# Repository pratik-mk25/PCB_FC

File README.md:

# PCB_FC
FLIGHT CONTROLLER DEMO

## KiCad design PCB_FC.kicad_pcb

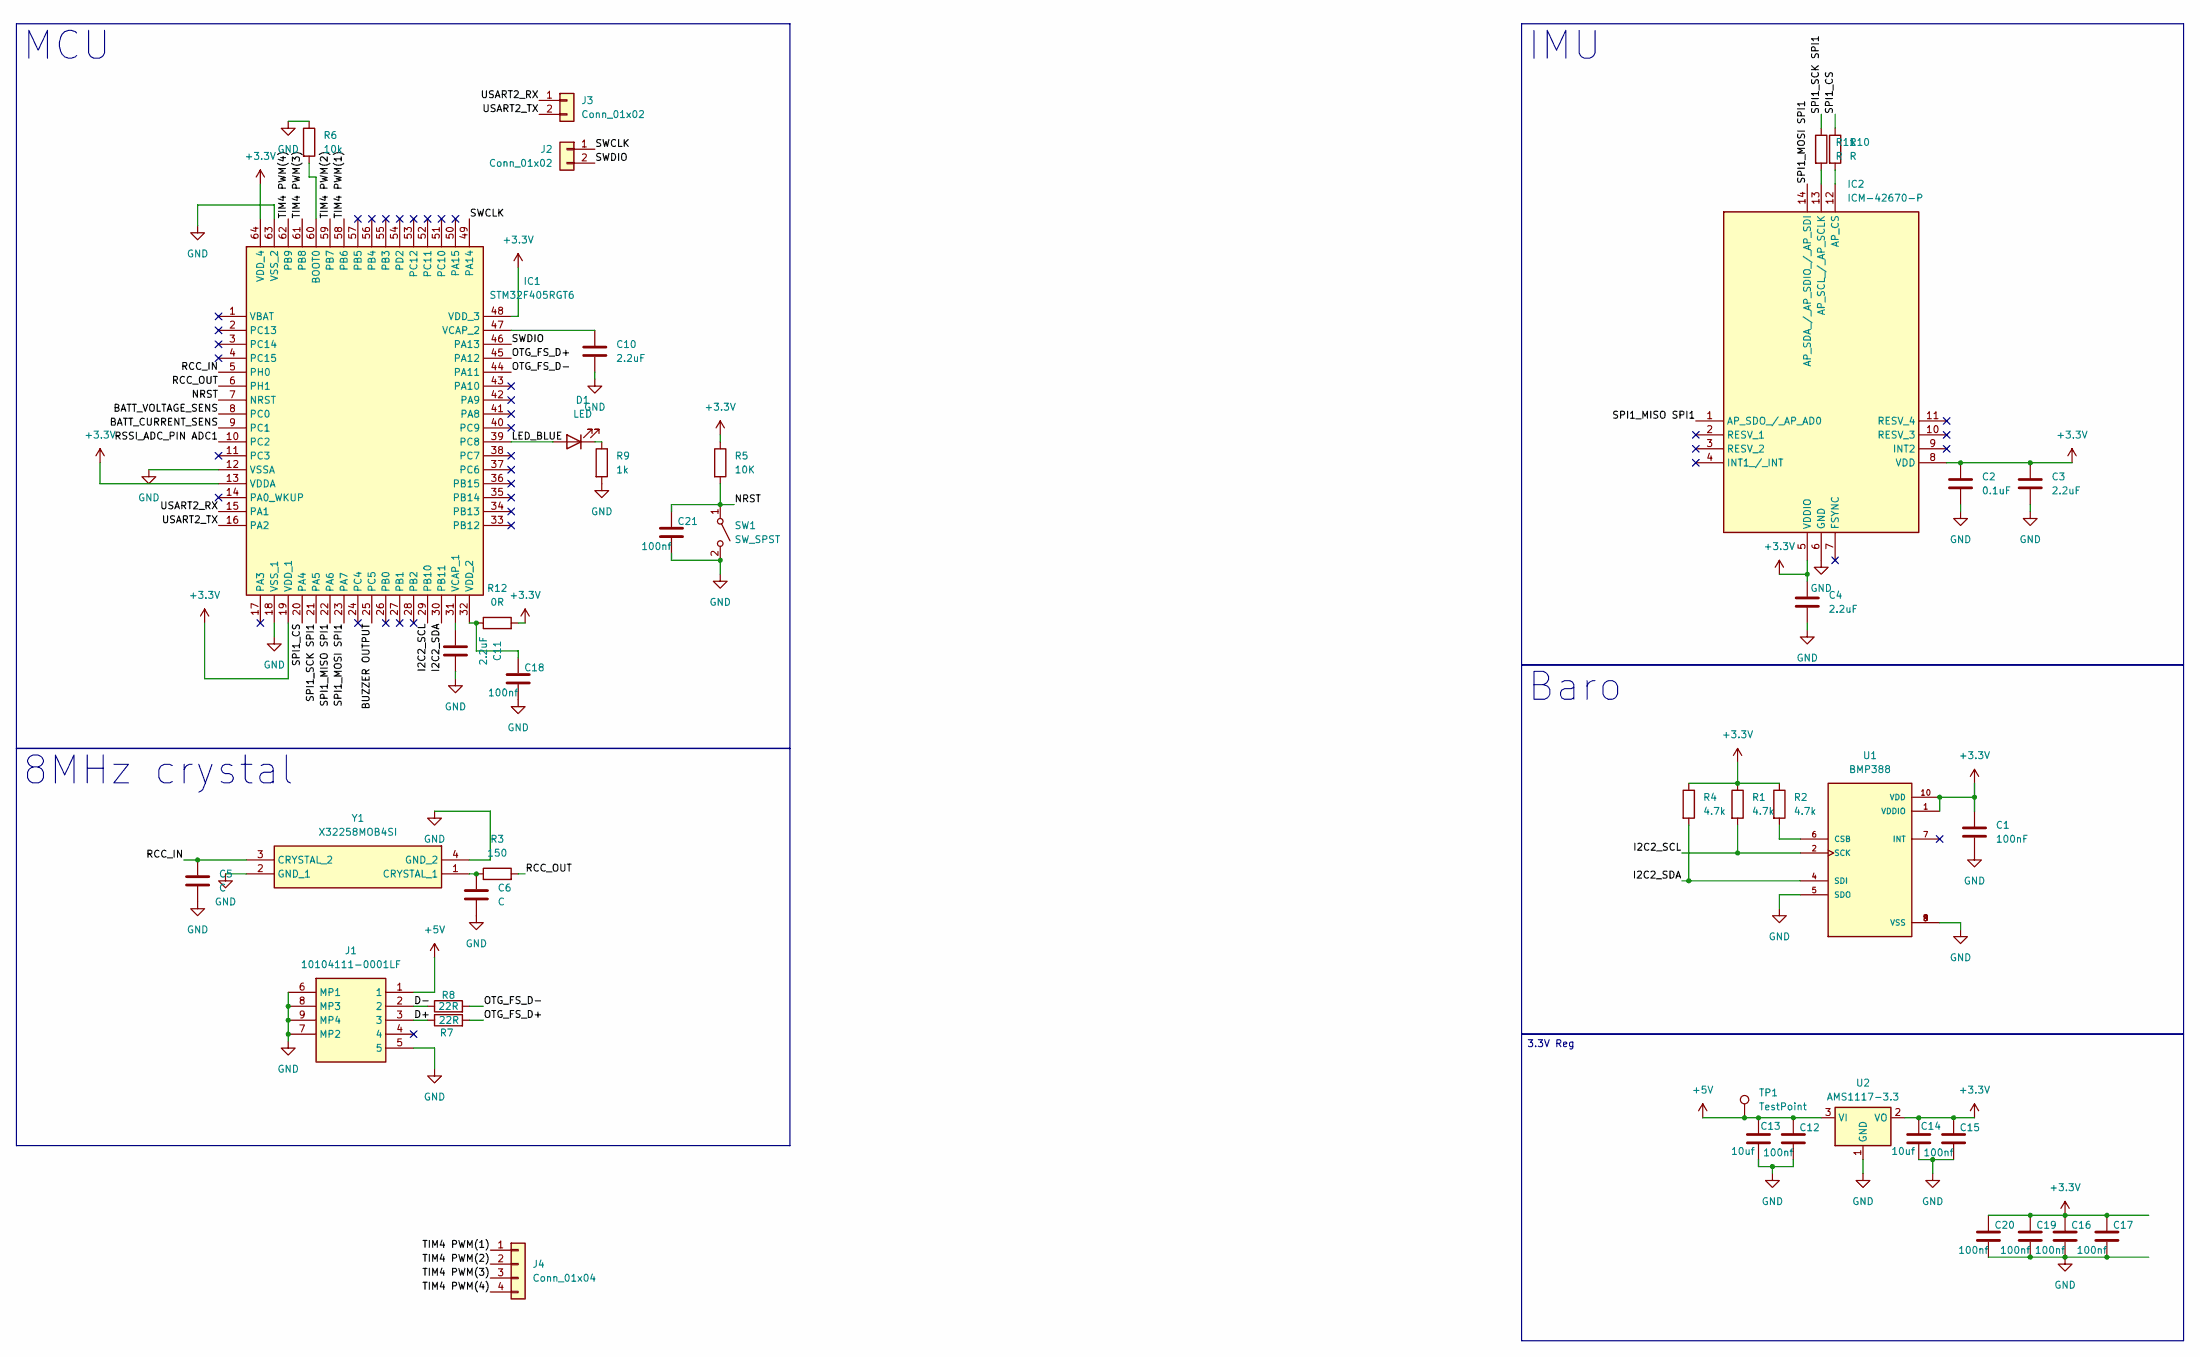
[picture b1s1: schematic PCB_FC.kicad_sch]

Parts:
C1: 100nF; C_0603_1608Metric_Pad1.08x0.95mm_HandSolder
C2: 0.1uF; C_0603_1608Metric_Pad1.08x0.95mm_HandSolder
C3, C4, C10, C11: 2.2uF; C_0603_1608Metric_Pad1.08x0.95mm_HandSolder
C5, C6: C; C_0603_1608Metric_Pad1.08x0.95mm_HandSolder
C12, C15, C16, C17, C18, C19, C20, C21: 100nf; C_0603_1608Metric_Pad1.08x0.95mm_HandSolder
C13, C14: 10uf; C_0805_2012Metric_Pad1.18x1.45mm_HandSolder
D1: LED; LED_0402_1005Metric_Pad0.77x0.64mm_HandSolder
IC1: STM32F405RGT6; Manufacturer_Part_Number STM32F405RGT6; Mouser Part Number 511-STM32F405RGT6
IC2: ICM-42670-P; Manufacturer_Part_Number ICM-42670-P; Mouser Part Number 410-ICM-42670-P
J1: 10104111-0001LF; Manufacturer_Part_Number 10104111-0001LF
J2, J3: Conn_01x02; PinHeader_1x02_P2.54mm_Vertical
J4: Conn_01x04
R1, R2, R4: 4.7k; R_0603_1608Metric_Pad0.98x0.95mm_HandSolder
R3: 150; R_0603_1608Metric_Pad0.98x0.95mm_HandSolder
R5: 10K; R_0603_1608Metric_Pad0.98x0.95mm_HandSolder
R6: 10k; R_0603_1608Metric_Pad0.98x0.95mm_HandSolder
R7, R8: 22R; R_0402_1005Metric_Pad0.72x0.64mm_HandSolder
R9: 1k; R_0603_1608Metric_Pad0.98x0.95mm_HandSolder
R10, R11: R; R_1206_3216Metric_Pad1.30x1.75mm_HandSolder
R12: 0R; R_0603_1608Metric_Pad0.98x0.95mm_HandSolder
SW1: SW_SPST; PTS636SKG25JSMTRLFS
TP1: TestPoint; Pin_D1.3mm_L11.3mm_W2.8mm_Flat
U1: BMP388; PARTREV 1.1
U2: AMS1117-3.3; SOT-223-3_TabPin2
Y1: X32258MOB4SI; Manufacturer_Part_Number X32258MOB4SI

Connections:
+3.3V: C1.1, C2.1, C3.1, C4.1, C14.1, C15.1, C16.1, C17.1, C19.1, C20.1, IC1.13 (VDDA), IC1.19 (VDD_1), IC1.48 (VDD_3), IC1.64 (VDD_4), IC2.5 (VDDIO), IC2.8 (VDD), R1.1, R2.1, R4.1, R5.1, R12.2, U1.1 (VDDIO), U1.10 (VDD), U2.2 (VO)
+5V: C12.1, C13.1, J1.1, TP1.1, U2.3 (VI)
/BATT_CURRENT_SENS: IC1.9 (PC1)
/BATT_VOLTAGE_SENS: IC1.8 (PC0)
/BUZZER OUTPUT: IC1.25 (PC5)
/D+: J1.3, R7.1
/D-: J1.2, R8.1
/I2C2_SCL: IC1.29 (PB10), R1.2, U1.2 (SCK)
/I2C2_SDA: IC1.30 (PB11), R4.2, U1.4 (SDI)
/LED_BLUE: D1.2 (A), IC1.39 (PC8)
/NRST: C21.1, IC1.7 (NRST), R5.2, SW1.1 (A)
/OTG_FS_D+: IC1.45 (PA12), R7.2
/OTG_FS_D-: IC1.44 (PA11), R8.2
/RCC_IN: C5.1, IC1.5 (PH0), Y1.3 (CRYSTAL_2)
/RCC_OUT: IC1.6 (PH1), R3.2
/RSSI_ADC_PIN ADC1: IC1.10 (PC2)
/SPI1_CS: IC1.20 (PA4), R10.1
/SPI1_MISO SPI1: IC1.22 (PA6), IC2.1 (AP_SDO_/_AP_AD0)
/SPI1_MOSI SPI1: IC1.23 (PA7), IC2.14 (AP_SDA_/_AP_SDIO_/_AP_SDI)
/SPI1_SCK SPI1: IC1.21 (PA5), R11.1
/SWCLK: IC1.49 (PA14), J2.1
/SWDIO: IC1.46 (PA13), J2.2
/TIM4 PWM(1): IC1.58 (PB6), J4.1
/TIM4 PWM(2): IC1.59 (PB7), J4.2
/TIM4 PWM(3): IC1.61 (PB8), J4.3
/TIM4 PWM(4): IC1.62 (PB9), J4.4
/USART2_RX: IC1.15 (PA1), J3.1
/USART2_TX: IC1.16 (PA2), J3.2
GND: C1.2, C2.2, C3.2, C4.2, C5.2, C6.2, C10.2, C11.2, C12.2, C13.2, C14.2, C15.2, C16.2, C17.2, C18.2, C19.2, C20.2, C21.2, IC1.12 (VSSA), IC1.18 (VSS_1), IC1.63 (VSS_2), IC2.6 (GND), J1.5, J1.6 (MP1), J1.7 (MP2), J1.8 (MP3), J1.9 (MP4), R6.1, R9.2, SW1.2 (B), U1.3 (VSS), U1.5 (SDO), U1.8 (VSS), U1.9 (VSS), U2.1 (GND), Y1.2 (GND_1), Y1.4 (GND_2)
unnamed: D1.1 (K), R9.1
unnamed: IC1.60 (BOOT0), R6.2
unnamed: C11.1, IC1.31 (VCAP_1)
unnamed: C10.1, IC1.47 (VCAP_2)
unnamed: C18.1, IC1.32 (VDD_2), R12.1
unnamed: IC2.12 (AP_CS), R10.2
unnamed: IC2.13 (AP_SCL_/_AP_SCLK), R11.2
unnamed: R2.2, U1.6 (CSB)
unnamed: C6.1, R3.1, Y1.1 (CRYSTAL_1)

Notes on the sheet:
MCU
IMU
Baro
8MHz crystal
3.3V Reg

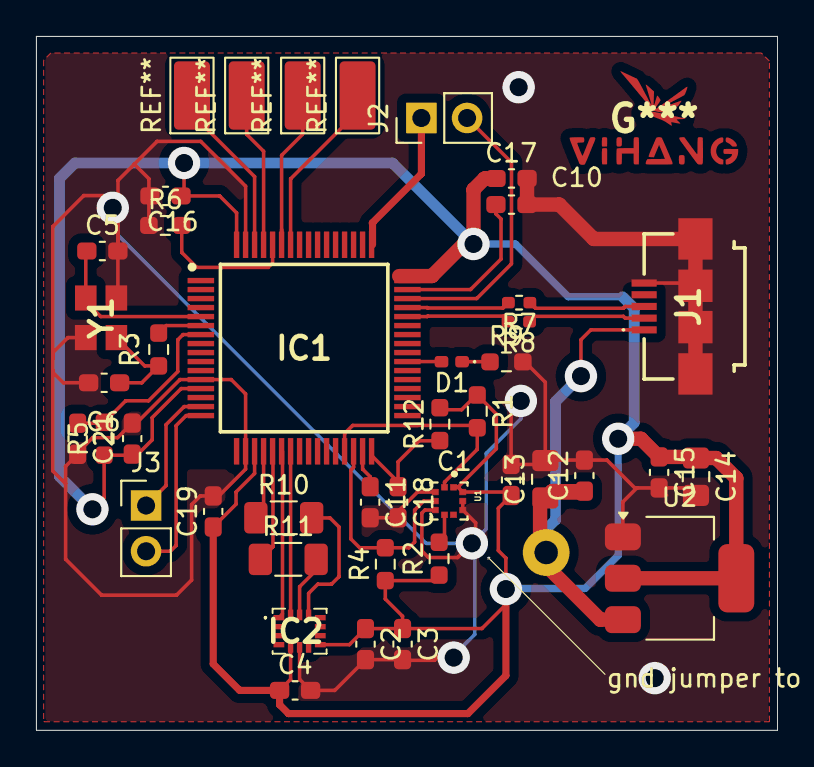
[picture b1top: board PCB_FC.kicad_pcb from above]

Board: 2 copper layers, 41.2 x 38.5 mm, 40 parts (1 on the bottom side), 30 nets.

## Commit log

2025-10-07 Basic design of schametic done
    1. Added folder for library
    2. Added USB with termination resistors
    3. Added Resistor network for bootstrapping and NRST
2025-10-10 Signal routing done
    1. Routing for IMU
    2. Differentially route pair for USB with termination resistor.
    3. HSE crystal oscillator added.
2025-10-12 PCB complete add logos
